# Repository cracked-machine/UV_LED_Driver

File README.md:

# UV LightBox

- Required Kicad Hardware library: https://github.com/cracked-machine/KicadLibrary
- Related SW project: https://github.com/cracked-machine/UV_LED_Driver_SW_STM32F051

This is a modular design that drives 4 panels of UV LEDS and 1 standard LED string.

<P>

</P>

- When the lightbox lid is open the standard LEDS are enabled. Their brightness can be adjusted using the rotary encoder control.
- When the lightbox lid is closed the UV LEDS are enabled.
- A timer will keep the UV LEDS enabled. When the timeout expires a buzzer will sound and the UV LEDS will be disabled. The timeout can be adjusted when using two buttons in steps of 10 seconds.
- A QVGA (2.2" 320x240) TFT LCD display shows the timer value.

- **OOTB operation runs on 5VDC. However, if higher voltage is required regulators U2 and U4 can be populated. These protect the LCD and Buzzer (JP3 and JP1 must be ON, JP2 and JP4 must be OFF)**

Module |Front |Back
:-----:|:-----:|:-----:
Controller||
Driver||

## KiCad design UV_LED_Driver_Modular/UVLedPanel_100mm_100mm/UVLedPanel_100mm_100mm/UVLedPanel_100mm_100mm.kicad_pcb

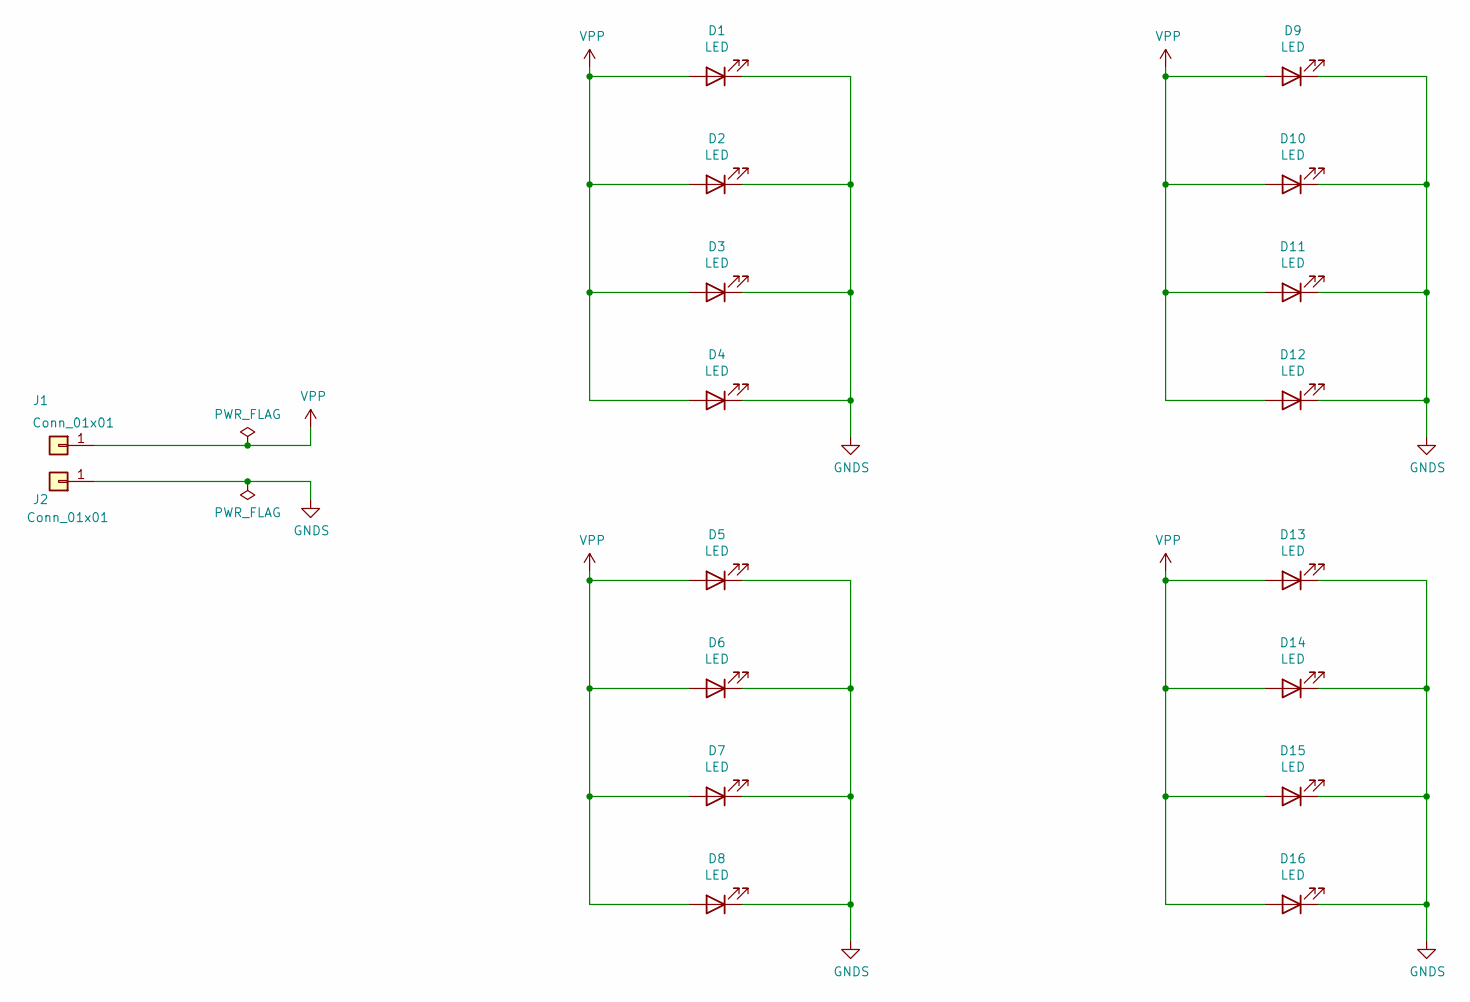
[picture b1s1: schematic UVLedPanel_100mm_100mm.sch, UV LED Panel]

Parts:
D1, D2, D3, D4, D5, D6, D7, D8, D9, D10, D11, D12, D13, D14, D15, D16: LED; LED_PLCC-2
J1, J2: Conn_01x01; TestPoint_Pad_4.0x4.0mm

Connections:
GNDS: D1.1 (K), D2.1 (K), D3.1 (K), D4.1 (K), D5.1 (K), D6.1 (K), D7.1 (K), D8.1 (K), D9.1 (K), D10.1 (K), D11.1 (K), D12.1 (K), D13.1 (K), D14.1 (K), D15.1 (K), D16.1 (K), J2.1
VPP: D1.2 (A), D2.2 (A), D3.2 (A), D4.2 (A), D5.2 (A), D6.2 (A), D7.2 (A), D8.2 (A), D9.2 (A), D10.2 (A), D11.2 (A), D12.2 (A), D13.2 (A), D14.2 (A), D15.2 (A), D16.2 (A), J1.1

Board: 2 copper layers, 18 parts (0 on the bottom side), 2 nets, no tracks yet.

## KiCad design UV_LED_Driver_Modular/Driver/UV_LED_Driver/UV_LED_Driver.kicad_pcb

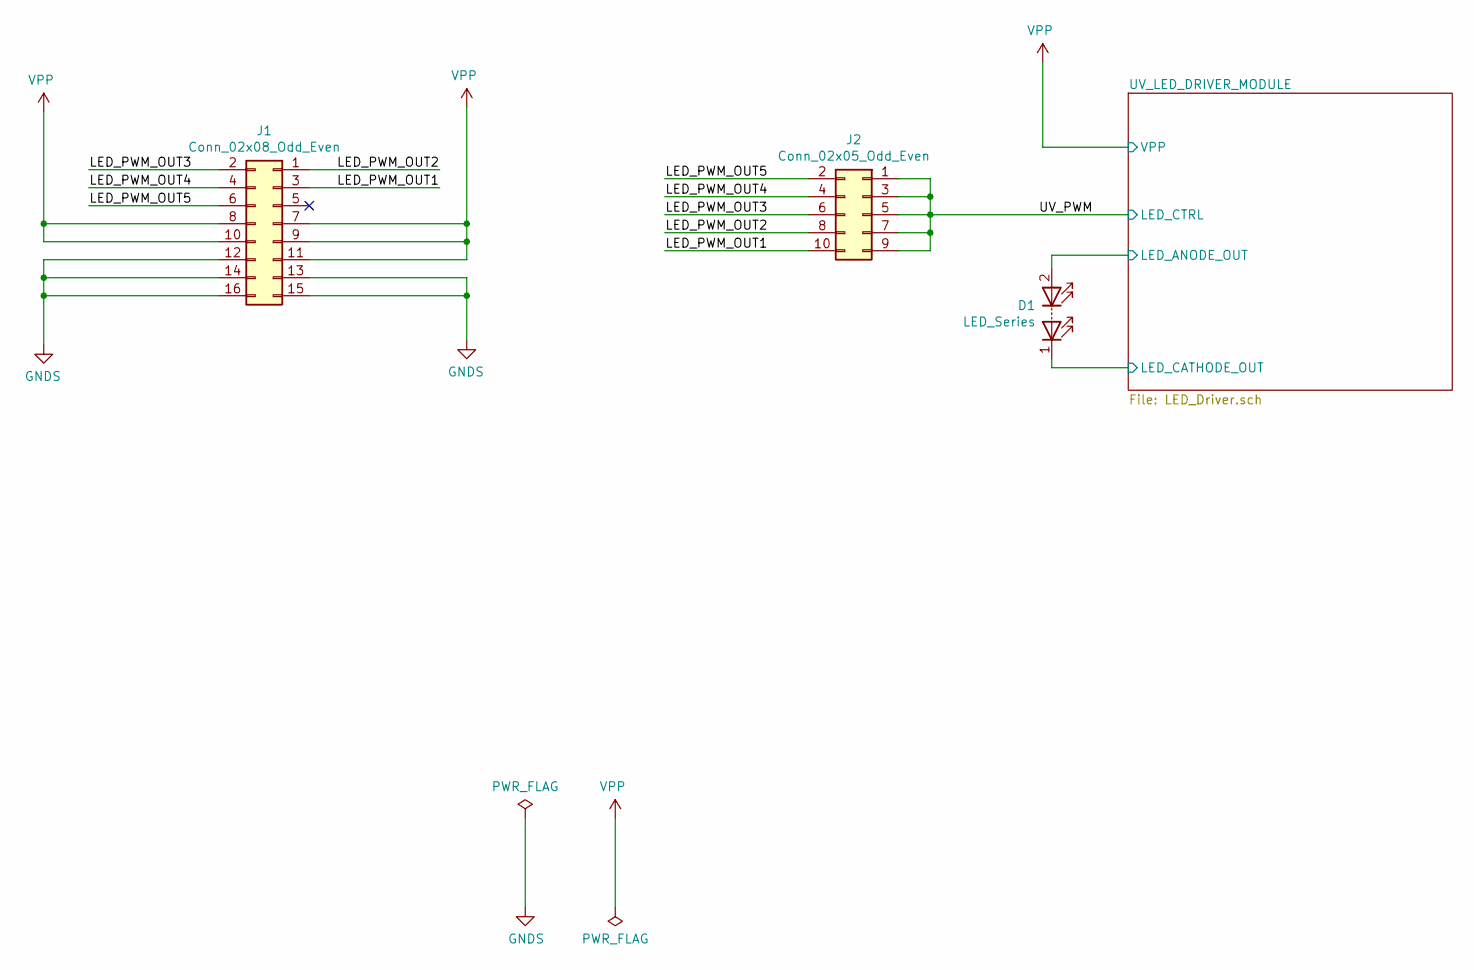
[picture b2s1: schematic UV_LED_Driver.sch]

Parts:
D1: LED_Series; Molex_Mini-Fit_Jr_5569-02A2_2x01_P4.20mm_Horizontal
J1: Conn_02x08_Odd_Even; PinHeader_2x08_P2.54mm_Vertical
J2: Conn_02x05_Odd_Even; PinHeader_2x05_P2.54mm_Vertical

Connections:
/LED_PWM_OUT1: J1.3, J2.10
/LED_PWM_OUT2: J1.1, J2.8
/LED_PWM_OUT3: J1.2, J2.6
/LED_PWM_OUT4: J1.4, J2.4
/LED_PWM_OUT5: J1.6, J2.2
/UV_LED_DRIVER_MODULE/LED_CATHODE_OUT: D1.1 (K); also elsewhere on the board
/UV_PWM: J2.1, J2.3, J2.5, J2.7, J2.9; also elsewhere on the board
GNDS: J1.12, J1.13, J1.14, J1.15, J1.16; also elsewhere on the board
VPP: D1.2 (A), J1.7, J1.8, J1.9, J1.10, J1.11; also elsewhere on the board

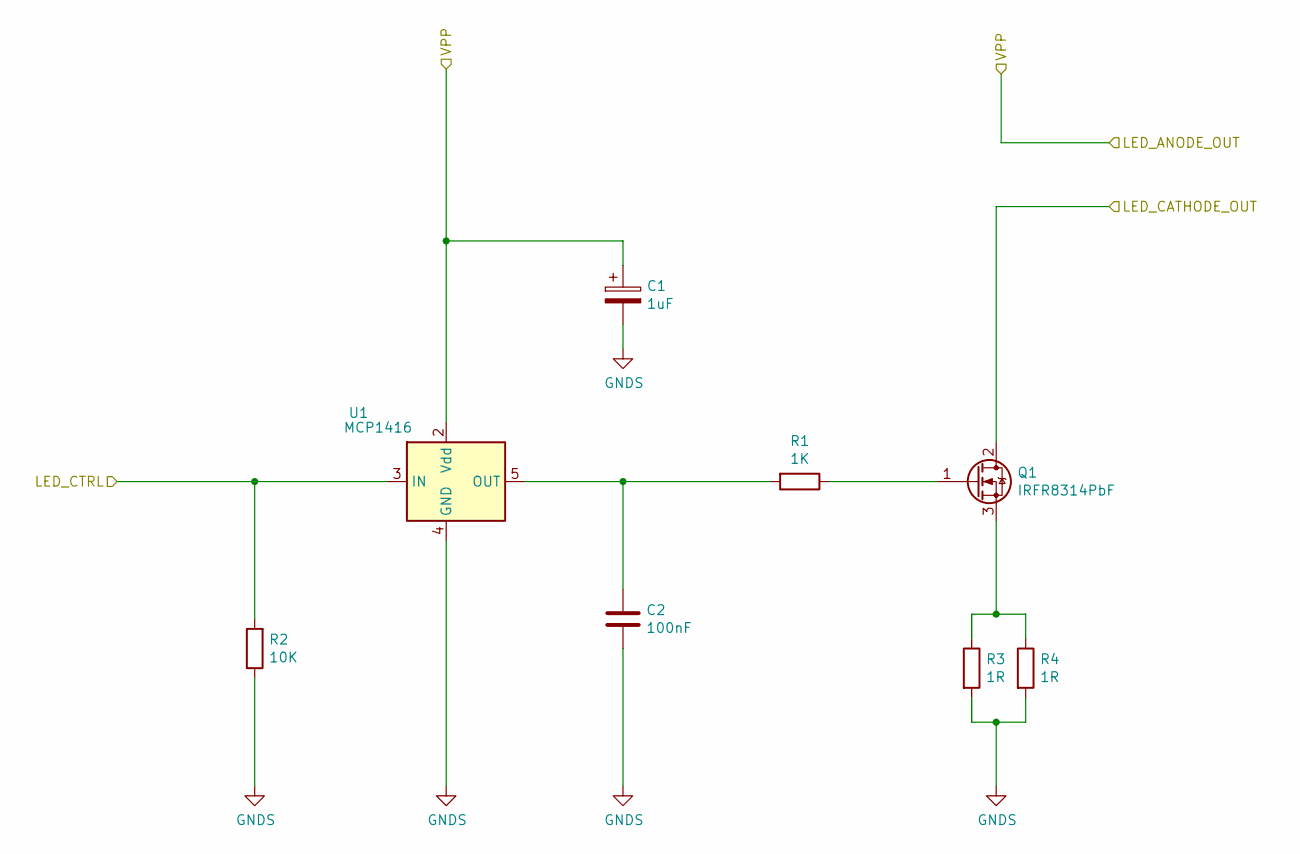
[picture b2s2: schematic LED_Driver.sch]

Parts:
C1: 1uF; C_1206_3216Metric_Pad1.42x1.75mm_HandSolder
C2: 100nF; C_1206_3216Metric_Pad1.42x1.75mm_HandSolder
Q1: IRFR8314PbF; TO-252-3_TabPin2
R1: 1K; R_1206_3216Metric_Pad1.42x1.75mm_HandSolder
R3, R4: 1R; R_1206_3216Metric_Pad1.42x1.75mm_HandSolder
R15: 10K; R_1206_3216Metric_Pad1.42x1.75mm_HandSolder
U1: MCP1416; SOT-23-5

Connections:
/UV_LED_DRIVER_MODULE/LED_CATHODE_OUT: Q1.2 (D); also elsewhere on the board
/UV_PWM: U1.3 (IN); also elsewhere on the board
GNDS: C1.2, C2.2, R3.2, R4.2, U1.4 (GND); also elsewhere on the board
unnamed: C2.1, R1.2, U1.5 (OUT)
unnamed: Q1.1 (G), R1.1
unnamed: Q1.3 (S), R3.1, R4.1
VPP: C1.1, U1.2 (Vdd); also elsewhere on the board

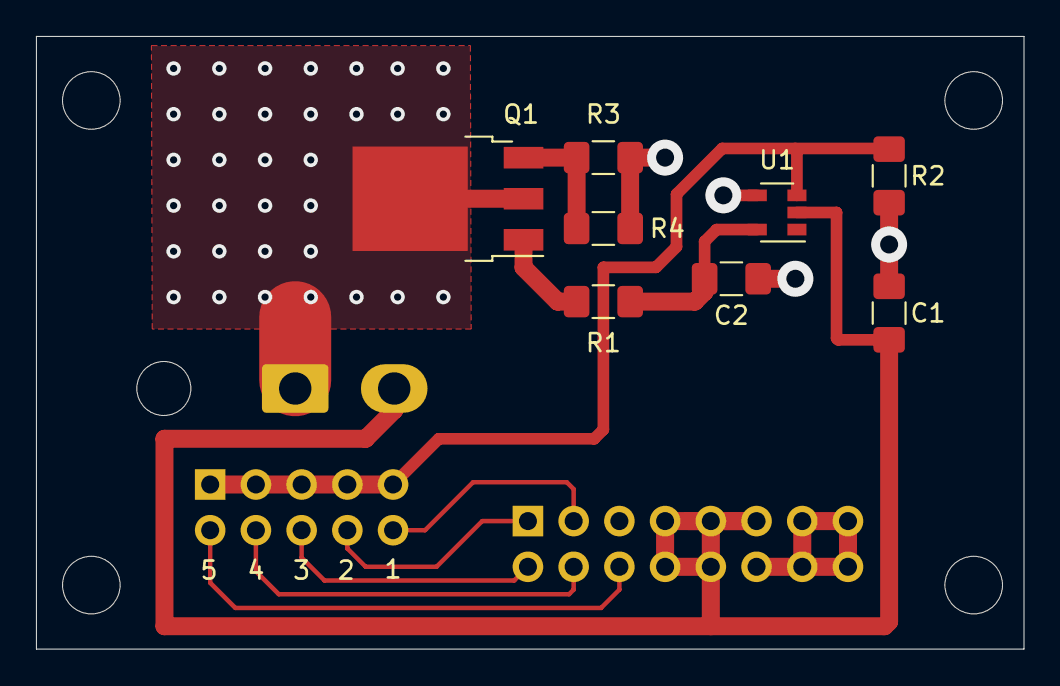
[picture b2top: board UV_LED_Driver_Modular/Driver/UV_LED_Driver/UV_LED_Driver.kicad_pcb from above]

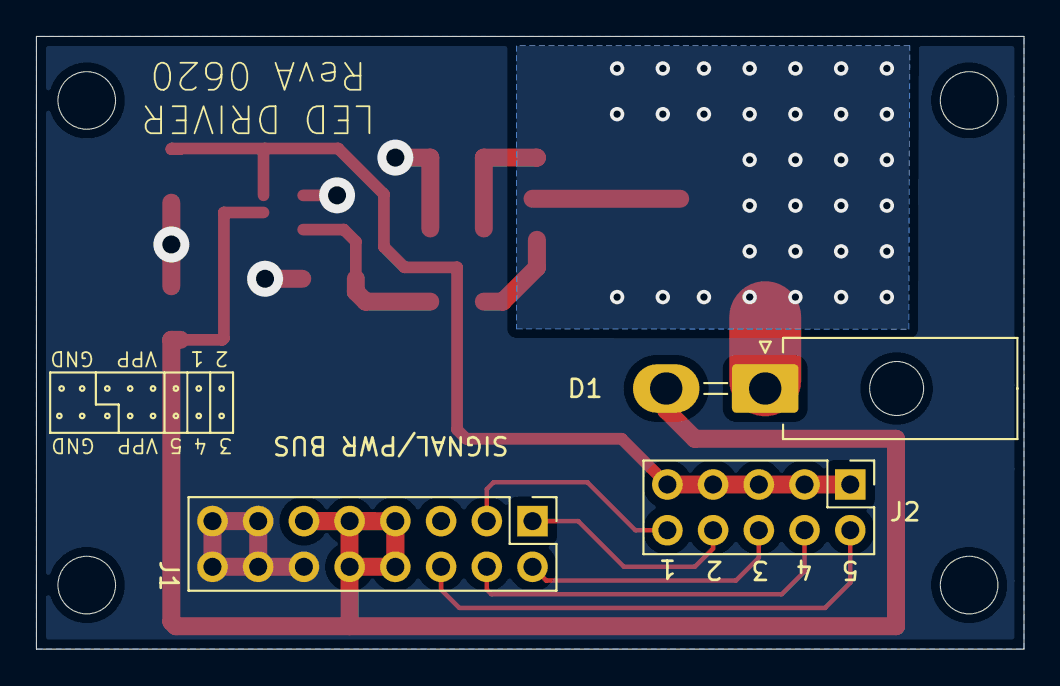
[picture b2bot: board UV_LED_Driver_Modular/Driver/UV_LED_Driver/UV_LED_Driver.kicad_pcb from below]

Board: 2 copper layers, 54.9 x 34.0 mm, 11 parts (3 on the bottom side), 12 nets.

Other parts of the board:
R2: 10K; R_1206_3216Metric_Pad1.42x1.75mm_HandSolder

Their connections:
/UV_PWM: R2.2; also elsewhere on the board
GNDS: R2.1; also elsewhere on the board

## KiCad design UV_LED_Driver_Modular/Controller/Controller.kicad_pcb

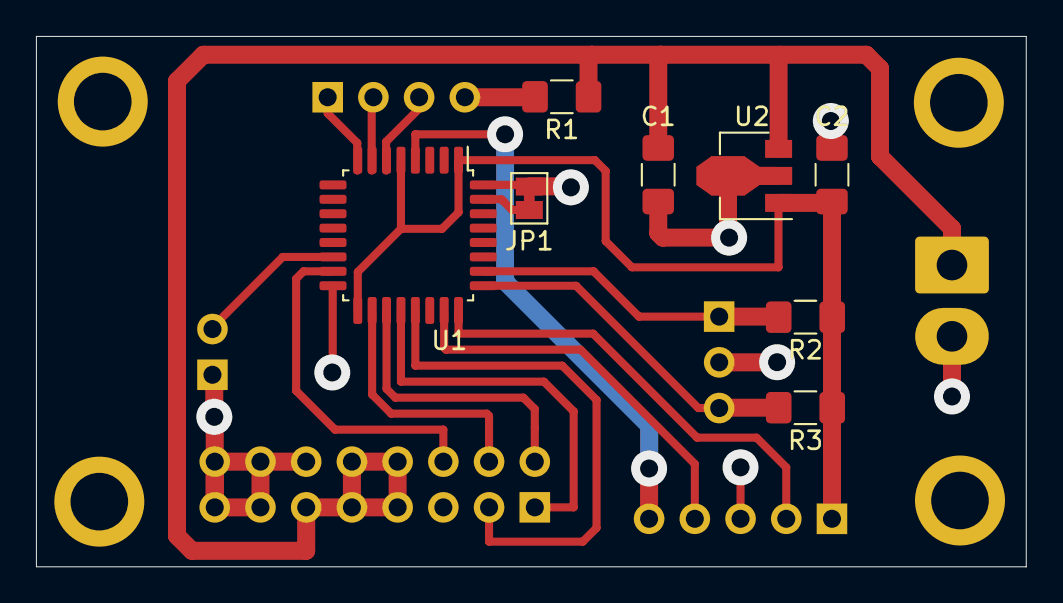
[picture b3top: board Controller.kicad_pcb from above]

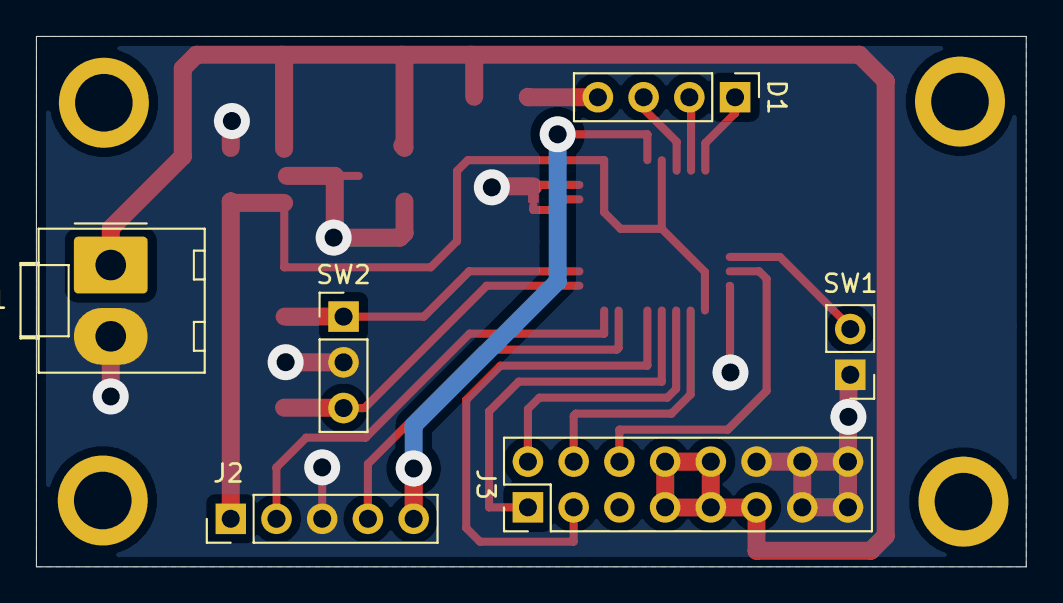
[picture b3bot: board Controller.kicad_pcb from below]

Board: 2 copper layers, 55.0 x 29.5 mm, 14 parts (6 on the bottom side), 19 nets.

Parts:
C1, C2: 1uF; C_1206_3216Metric_Pad1.42x1.75mm_HandSolder
D1: LED_RGBA; PinHeader_1x04_P2.54mm_Vertical
J1: Barrel_Jack; Molex_KK-396_A-41791-0002_1x02_P3.96mm_Vertical
J2: Conn_01x05; PinHeader_1x05_P2.54mm_Vertical
J3: Conn_02x08_Odd_Even; PinHeader_2x08_P2.54mm_Vertical
JP1: Jumper_NC_Small; SolderJumper-2_P1.3mm_Bridged_Pad1.0x1.5mm
R1: 2K2; R_1206_3216Metric_Pad1.42x1.75mm_HandSolder
R2, R3: 10K; R_1206_3216Metric_Pad1.42x1.75mm_HandSolder
SW1: SW_SPST; PinHeader_1x02_P2.54mm_Vertical
SW2: Rotary_Encoder; PinHeader_1x03_P2.54mm_Vertical
U1: STM32F051K8Tx; LQFP-32_7x7mm_P0.8mm
U2: L78L33_SOT89; SOT-89-3

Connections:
+3V3: C2.1, J2.1, R2.1, R3.1, U1.1, U1.5, U1.17, U2.1
/LED_Controller_Module/ENABLE_LED: SW1.2, U1.14
/LED_Controller_Module/ENC_A: R2.2, SW2.1, U1.26
/LED_Controller_Module/ENC_B: R3.2, SW2.3, U1.25
/LED_Controller_Module/NRST: J2.5, U1.4
/LED_Controller_Module/STATUS_BLUE: D1.3, U1.6
/LED_Controller_Module/STATUS_GREEN: D1.2, U1.7
/LED_Controller_Module/STATUS_RED: D1.1, U1.8
/LED_Controller_Module/SWCLK: J2.2, U1.24
/LED_Controller_Module/SWDIO: J2.4, U1.23
/LED_PWM_OUT1: J3.3, U1.21
/LED_PWM_OUT2: J3.1, U1.20
/LED_PWM_OUT3: J3.2, U1.19
/LED_PWM_OUT4: J3.4, U1.18
/LED_PWM_OUT5: J3.6, U1.15
GNDS: C1.2, C2.2, J1.2, J2.3, J3.12, J3.13, J3.14, J3.15, J3.16, JP1.1, SW1.1, SW2.2, U1.16, U1.32, U2.2
unnamed: D1.4, R1.2
unnamed: JP1.2, U1.31
VPP: C1.1, J1.1, J3.7, J3.8, J3.9, J3.10, J3.11, R1.1, U2.3

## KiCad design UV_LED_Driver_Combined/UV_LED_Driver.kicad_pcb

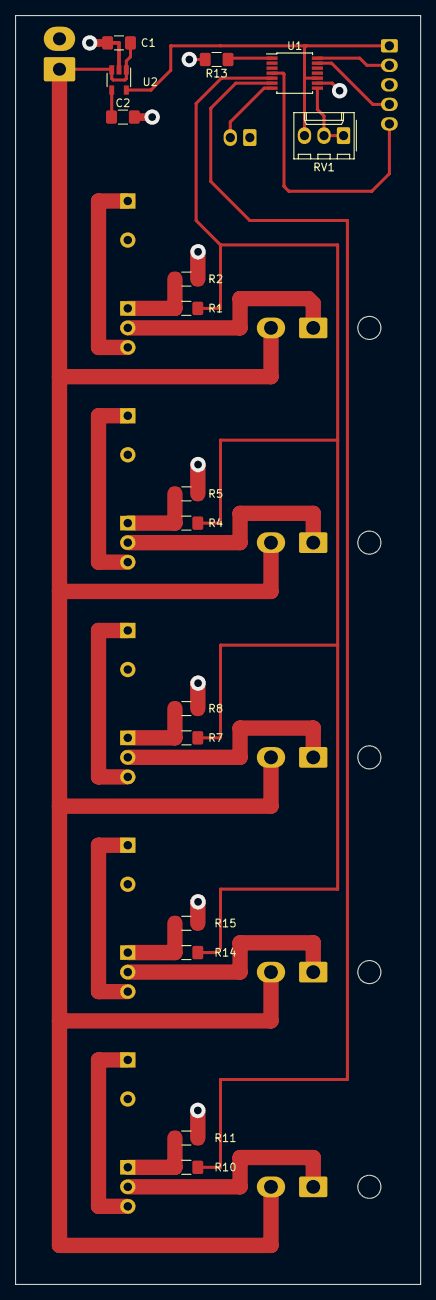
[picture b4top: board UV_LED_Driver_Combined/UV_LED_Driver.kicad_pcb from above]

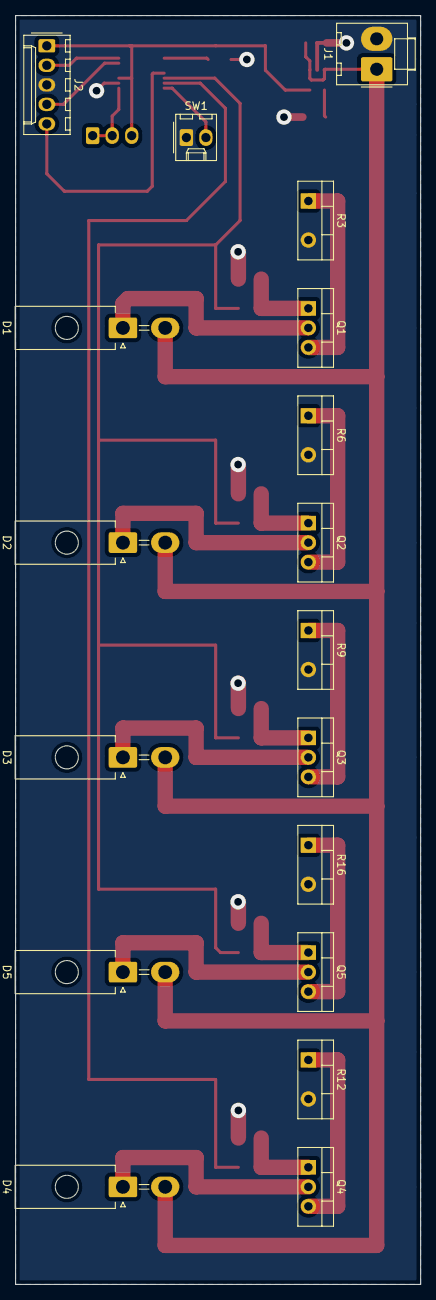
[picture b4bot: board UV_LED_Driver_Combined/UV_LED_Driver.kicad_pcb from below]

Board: 2 copper layers, 52.7 x 165.1 mm, 34 parts (18 on the bottom side), 27 nets.

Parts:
C1, C2: 1uF; C_1206_3216Metric_Pad1.42x1.75mm_HandSolder
D1, D2, D3, D4, D5: LED_Connector; Molex_Mini-Fit_Jr_5569-02A2_2x01_P4.20mm_Horizontal
J1: Barrel_Jack; Molex_KK-396_A-41791-0002_1x02_P3.96mm_Vertical
J2: Conn_01x05; Molex_KK-254_AE-6410-05A_1x05_P2.54mm_Vertical
Q1, Q2, Q3, Q4, Q5: IPP80N03S4L-03; TO-220-3_Vertical
R1, R4, R7, R10, R14: 100R; R_1206_3216Metric_Pad1.42x1.75mm_HandSolder
R2, R5, R8, R11, R13, R15: 10K; R_1206_3216Metric_Pad1.42x1.75mm_HandSolder
R3, R6, R9, R12, R16: R100; TO-220-2_Vertical
RV1: B10K; Molex_KK-254_AE-6410-03A_1x03_P2.54mm_Vertical
SW1: SW_SPST; Molex_KK-254_AE-6410-02A_1x02_P2.54mm_Vertical
U1: STM32L011D4Px; TSSOP-14_4.4x5mm_P0.65mm
U2: LP3992-33B5F; TSOT-23-5

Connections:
+5V: C1.1, D1.2, D2.2, D3.2, D4.2, D5.2, J1.1, U2.1, U2.3
/LED_CTRL: R10.2, U1.6
/LED_Controller/3V3: J2.1, RV1.3, U1.10, U2.5
/LED_Controller/LED_ADC: RV1.1, RV1.2, U1.8
/LED_Controller/LID_SW: SW1.2, U1.7
/LED_Controller/NRST: J2.5, U1.4
/LED_Controller/SWCLK: J2.2, U1.14
/LED_Controller/SWDIO: J2.4, U1.13
/UV_LED_CTRL: R1.2, R4.2, R7.2, R14.2, U1.5
GNDS: C1.2, C2.2, J1.2, J2.3, R2.1, R3.2, R5.1, R6.2, R8.1, R9.2, R11.1, R12.2, R13.2, R15.1, R16.2, SW1.1, U1.9, U2.2
unnamed: C2.1, U2.4
unnamed: D1.1, Q1.2
unnamed: D2.1, Q2.2
unnamed: D3.1, Q3.2
unnamed: D4.1, Q4.2
unnamed: D5.1, Q5.2
unnamed: Q1.1, R1.1, R2.2
unnamed: Q1.3, R3.1
unnamed: Q2.1, R4.1, R5.2
unnamed: Q2.3, R6.1
unnamed: Q3.1, R7.1, R8.2
unnamed: Q3.3, R9.1
unnamed: Q4.1, R10.1, R11.2
unnamed: Q4.3, R12.1
unnamed: Q5.1, R14.1, R15.2
unnamed: Q5.3, R16.1
unnamed: R13.1, U1.1

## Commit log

2020-04-25 Created Modular designs
    Combined project reuses modular design schematics
    - UV_LED_Driver_Modular/Driver/LED_Driver.sch
    - UV_LED_Driver_Modular/Controller/LED_Controller.sch
2020-04-26 Changed TO225 NPN (MJE340) to SOT223 NPN (PZT2222A)
2020-04-26 changed controller module LDO from SOT23 to SOT223
2020-04-29 added IRS4427 mosfet gate driver to controller design
2020-05-09 docs update
2020-06-16 hw update
    modified output pin header
2020-06-21 HW Updates
    ReRouted 5V to TFT VCC and LED pins.
2020-06-24 hw update
    controller revb
2020-06-27 modified headers
2020-06-27 Updated prototype designs for fab
    updated readme
2020-07-06 added pull down resistor to MCU to prevent buzzer from sounding at boot
2020-08-23 Added custom 100mm x 100mm LED panel
